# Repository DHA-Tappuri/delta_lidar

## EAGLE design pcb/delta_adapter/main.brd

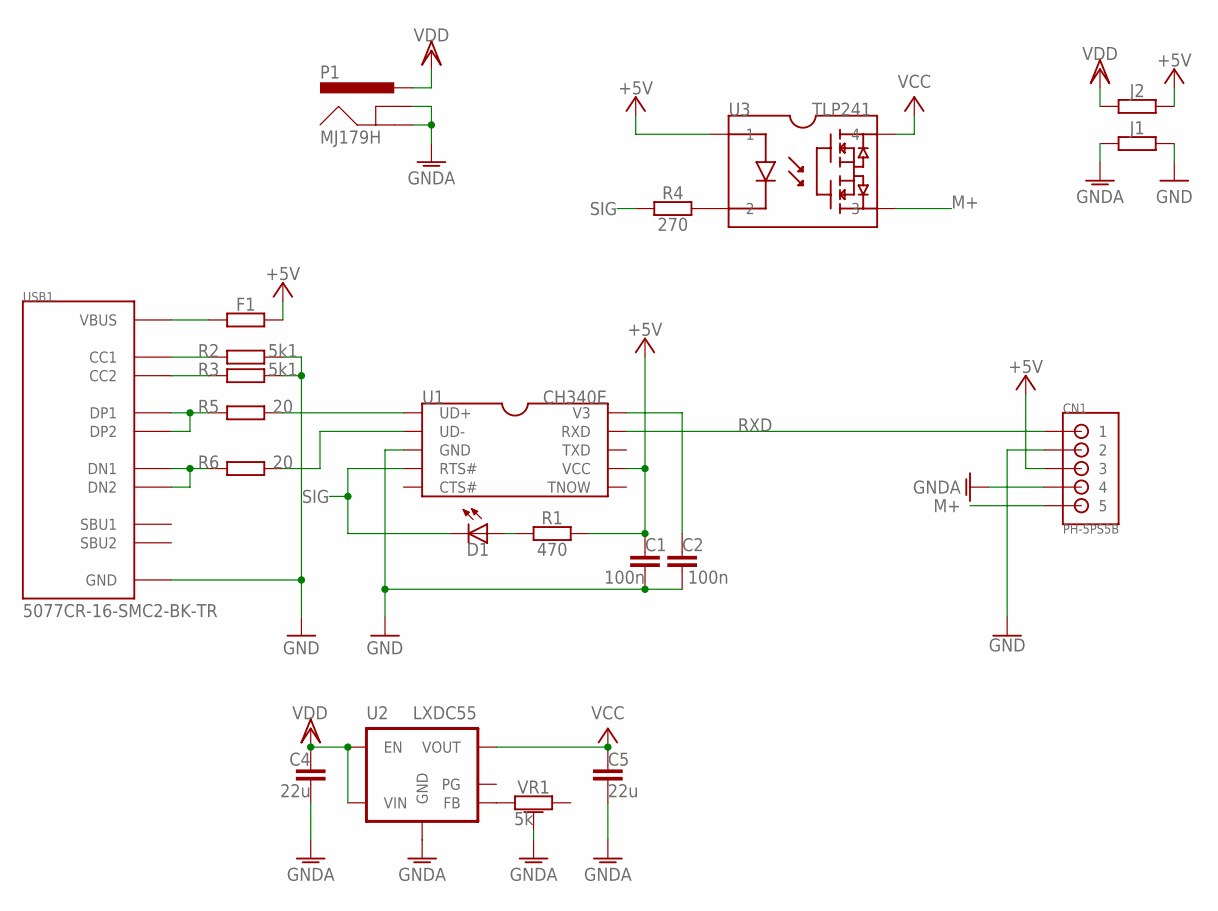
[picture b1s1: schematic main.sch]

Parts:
C1, C2: 100n; C1608
C4, C5: 22u; C1608
CN1: PH-5PS5B; S5B-PH-K-S
D1: LED1608B
F1: 5k1; R3225
J1, J2: JUMPER2012; J2012
P1: DC-JACKMJ179PH; MJ179PH; PART# MJ179H
R1: 470; R1608
R2, R3: 5k1; R1608
R4: 270; R1608
R5, R6: 20; R1608
U1: CH340EMSOP; MSOP-05-10P; PART# CH340E
U2: LXDC55FAAA-203SMD-GND; LXDC55FAAA-203-GND; PART# LXDC55
U3: TLP241ADIP; DIP-4P; PART# TLP241
USB1: USB1; 5077CR-16-SMC2-BK-TR; PART# 5077CR-16-SMC2-BK-TR
VR1: 5k; SEMIVR_3296W

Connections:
+5V: C1.P$1 (1), CN1.3, F1.P$2 (2), J2.P$2 (2), R1.P$1 (1), U1.P$7 (VCC), U3.P$1 (1)
GND: C1.P$2 (2), C2.P$2 (2), CN1.2, J1.P$2 (2), R2.P$2 (2), R3.P$2 (2), U1.P$3 (GND), USB1.A1_B12 (GND), USB1.B1_A12 (GND), USB1.P$13 (GND), USB1.P$14 (GND), USB1.P$15 (GND), USB1.P$16 (GND), USB1.P$17 (GND), USB1.P$18 (GND), USB1.P$19 (GND), USB1.P$20 (GND)
GNDA: C4.P$2 (2), C5.P$2 (2), CN1.4, J1.P$1 (1), P1.BREAK (GNDBREAK), P1.BREAK1 (GNDBREAK), P1.GND, P1.GND1 (GND), U2.P$15 (GND), VR1.P$3 (3)
M+: CN1.5, U3.P$3 (3)
unnamed: D1.P$1 (A), R1.P$2 (2)
unnamed: R6.P$1 (1), USB1.A7 (DN1), USB1.B7 (DN2)
unnamed: C2.P$1 (1), U1.P$10 (V3)
unnamed: R2.P$1 (1), USB1.A5 (CC1)
unnamed: R3.P$1 (1), USB1.B5 (CC2)
unnamed: R5.P$1 (1), USB1.A6 (DP1), USB1.B6 (DP2)
unnamed: R6.P$2 (2), U1.P$2 (UD-)
unnamed: R5.P$2 (2), U1.P$1 (UD+)
unnamed: R4.P$2 (2), U3.P$2 (2)
unnamed: F1.P$1 (1), USB1.A4_B9 (VBUS), USB1.B4_A9 (VBUS)
unnamed: U2.P$11 (FB), VR1.P$2 (2)
RXD: CN1.1, U1.P$9 (RXD)
SIG: D1.P$2 (K), R4.P$1 (1), U1.P$4 (RTS#)
VCC: C5.P$1 (1), U2.P$7 (VOUT), U2.P$8 (VOUT), U2.P$9 (VOUT), U3.P$4 (4)
VDD: C4.P$1 (1), J2.P$1 (1), P1.VCC (PWR), P1.VCC1 (PWR), U2.P$1 (EN), U2.P$3 (VIN), U2.P$4 (VIN), U2.P$5 (VIN)

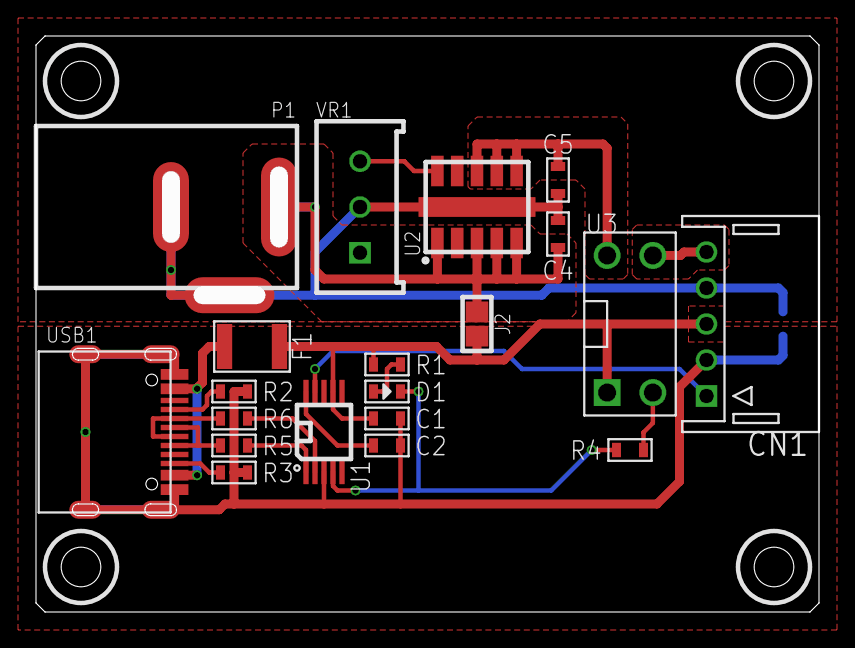
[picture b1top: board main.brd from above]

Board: 2 copper layers, 42.5 x 31.0 mm, 21 parts (1 on the bottom side), 19 nets.

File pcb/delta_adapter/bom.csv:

Part,Part #,Value,Qty.,Price,Price/Unit,Package,Device,URL
"C1, C2",GRM188F11H104ZA01,100n,2,2.5,5,1608,CAPACITOR,https://akizukidenshi.com/catalog/g/g113374/
"C4,C5",GRM188R61A226ME,22u,2,10,20,1608,CAPACITOR,https://akizukidenshi.com/catalog/g/g107922/
CN1,B5B-PH-K-S,5P,1,15,15,TH,CONNECTOR,https://akizukidenshi.com/catalog/g/g112805/
D1,OSG50603C1E,RED,1,10,10,1608,LED,https://akizukidenshi.com/catalog/g/g108275/
F1,MF-NSMF050-2,500mA,1,27.5,27.5,3216,POLYSWITCH,https://akizukidenshi.com/catalog/g/g115300/
P1,MJ179PH,4A,1,40,40,TH,DC-JACK,https://akizukidenshi.com/catalog/g/g106568/
"R1,R4",RK73B1JTTD201J,200,2,5,10,1608,RESISTER,https://www.sengoku.co.jp/mod/sgk_cart/detail.php?code=EEHD-57FZ
"R2,R3",RK73B1JTTD512J,5.1k,2,5,10,1608,RESISTER,https://www.sengoku.co.jp/mod/sgk_cart/detail.php?code=EEHD-57GS
"R5,R6",RK73B1JTTD200J,20,2,5,10,1608,RESISTER,https://www.sengoku.co.jp/mod/sgk_cart/detail.php?code=EEHD-57FC
U1,CH340E,,1,90,90,MSOP10,USB INTERFACE,https://akizukidenshi.com/catalog/g/g113543/
U2,LXDC55FAAA-203,,1,350,350,SMD,DC-DC CONVERTER,https://akizukidenshi.com/catalog/g/g109577/
U3,TLP241A,,1,140,140,DIP4,PHOTO COUPLER,https://akizukidenshi.com/catalog/g/g111516/
USB1,5077CR-16-SMC2-BK-TR,,1,110,110,SMD,USB CONNECTOR,https://akizukidenshi.com/catalog/g/g114356/
VR1,3296W-1-502LF,5k,1,120,120,TH,VARIABLE RESISTER,https://akizukidenshi.com/catalog/g/g100974/

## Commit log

2025-02-17 working commit
2025-02-20 add config and launch
